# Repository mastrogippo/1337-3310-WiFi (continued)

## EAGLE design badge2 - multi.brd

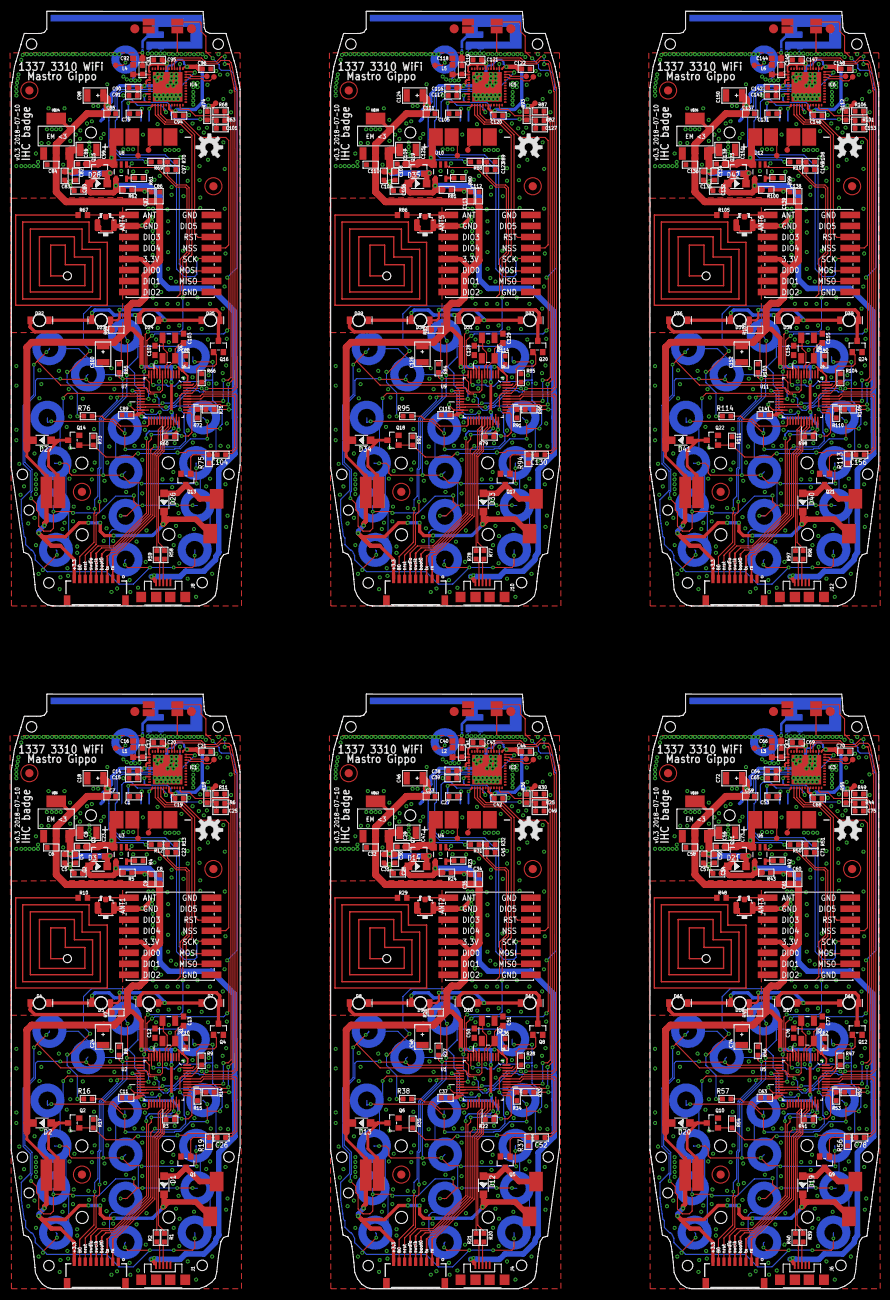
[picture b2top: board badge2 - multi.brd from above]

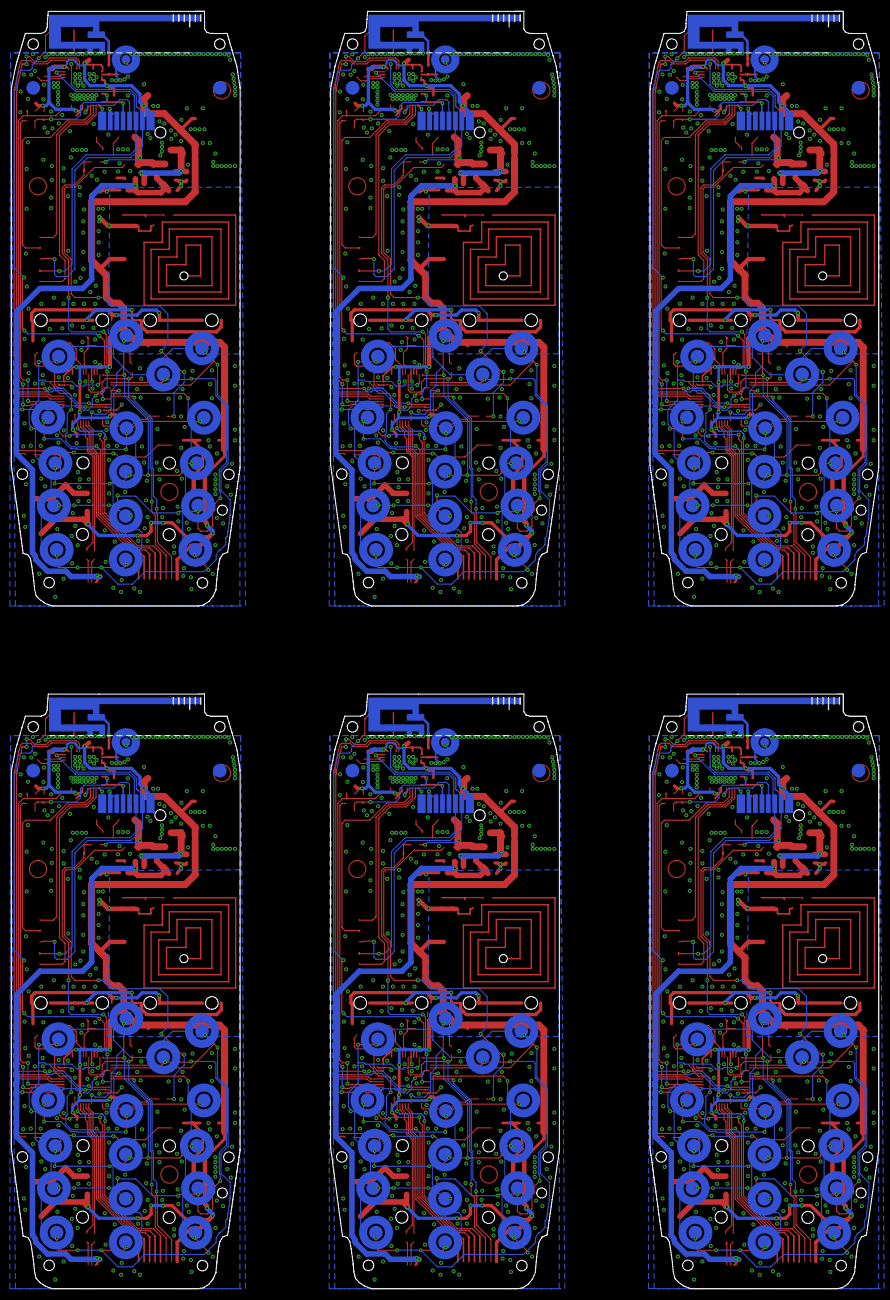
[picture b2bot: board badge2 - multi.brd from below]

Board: 2 copper layers, 157.6 x 232.0 mm, 474 parts (12 on the bottom side), 378 nets.

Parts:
ANT1, ANT2, ANT3, ANT4, ANT5, ANT6: U-FL; U-FL3P-SMD-2.6X2.6X1.0MM
C1, C2, C3, C4, C6, C7, C8, C21, C26, C27, C28, C29, C30, C32, C33, C34, C44, C52, C53, C54, C55, C56, C58, C59, C60, C70, C78, C79, C80, C81, C82, C84, C85, C86, C96, C104, C105, C106, C107, C108, C110, C111, C112, C122, C130, C131, C132, C133, C134, C136, C137, C138, C148, C156: 4.7uf; C0603
C5, C9, C10, C11, C15, C19, C20, C22, C25, C31, C35, C36, C37, C39, C42, C43, C45, C49, C57, C61, C62, C63, C65, C68, C69, C71, C75, C83, C87, C88, C89, C91, C94, C95, C97, C101, C109, C113, C114, C115, C117, C120, C121, C123, C127, C135, C139, C140, C141, C143, C146, C147, C149, C153: 100nf; C0603
C12, C13, C50, C51, C76, C77, C102, C103, C128, C129, C154, C155: 18pF; 0603
C14, C38, C64, C90, C116, C142: 10uf; C0603
C16, C40, C66, C92, C118, C144: 2.7p; C0603
C17, C41, C67, C93, C119, C145: 4.7PF; C0603
C18, C23, C24, C46, C47, C48, C72, C73, C74, C98, C99, C100, C124, C125, C126, C150, C151, C152: 22uf; AVX-B
D1, D2, D3, D12, D13, D14, D19, D20, D21, D26, D27, D28, D33, D34, D35, D40, D41, D42: NRVTS245ESFT3G; SOD-123
D4, D5, D6, D7, D8, D9, D10, D11, D15, D16, D17, D18, D22, D23, D24, D25, D29, D30, D31, D32, D36, D37, D38, D39: LED-BOTTOM-1206; LED-1206
FID1, FID2, FID3, FID4, FID5, FID6, FID7, FID8, FID9, FID10, FID11, FID12, FID13, FID14, FID15, FID16, FID17, FID18: FIDUCIAL1.5X3; FIDUCIAL-1.5X3
IC1, IC2, IC3, IC4, IC5, IC6: ESP32-PICO-D4; ESP32-PICO-D4_1
J1, J4, J6, J8, J10, J12: USB-MICROB
J2, J3, J5, J7, J9, J11: 1X01_POGOPIN_HOLE_0.58_DIA
L1, L2, L3, L4, L5, L6: 1.6nH; C0603K
Q1, Q2, Q4, Q5, Q6, Q8, Q9, Q10, Q12, Q13, Q14, Q16, Q17, Q18, Q20, Q21, Q22, Q24: CJ2302; SOT-23
Q3, Q7, Q11, Q15, Q19, Q23: FDN340P; SOT-23
R1, R2, R6, R7, R20, R21, R25, R26, R39, R40, R44, R45, R58, R59, R63, R64, R77, R78, R82, R83, R96, R97, R101, R102: 22R; R0603
R3, R22, R41, R60, R79, R98: 1.5K; R0603
R4, R23, R42, R61, R80, R99: 2K; R0603
R5, R9, R11, R16, R18, R19, R24, R28, R30, R36, R37, R38, R43, R47, R49, R55, R56, R57, R62, R66, R68, R74, R75, R76, R81, R85, R87, R93, R94, R95, R100, R104, R106, R112, R113, R114: 10K; R0603
R8, R27, R46, R65, R84, R103: 10K 1/10W; R0603
R10, R29, R48, R67, R86, R105: 0; R0603
R12, R13, R14, R15, R17, R31, R32, R33, R34, R35, R50, R51, R52, R53, R54, R69, R70, R71, R72, R73, R88, R89, R90, R91, R92, R107, R108, R109, R110, R111: 100K 1/10W; R0603
TP1, TP2, TP3, TP4, TP5, TP6, TP7, TP8, TP9, TP10, TP11, TP12, TP13, TP14, TP15, TP16, TP17, TP18, TP19, TP20, TP21, TP22, TP23, TP24, TP25, TP26, TP27, TP28, TP29, TP30, TP31, TP32, TP33, TP34, TP35, TP36: TEST-POINT3X4; PAD.03X.04
U1, U2, U5, U7, U9, U11: STM32F103CBT6; QFP50P900X900X160-48N
U3, U4, U6, U8, U10, U12: MCP73831; SOT23-5
U$1, U$7, U$13, U$19, U$25, U$31: 3310PANEL; 3310LCD
U$2, U$8, U$14, U$20, U$26, U$32: WIRELESS-LORA-RFM95W#SMD
U$3, U$9, U$15, U$21, U$27, U$33: INVERTED_F_ANTENNA+2; DN007+2
U$4, U$10, U$16, U$22, U$28, U$34: JST-09-PIN-HORIZONTAL; JST-09-SMD-HORI-1.0MM
U$5, U$11, U$17, U$23, U$29, U$35: OSHW-LOGO-M
U$6, U$12, U$18, U$24, U$30, U$36: CJT1117-3.3-SOT223; SOT-223
Y1, Y2, Y3, Y4, Y5, Y6: 8MHz; CRYSTAL-SMD-5X3.2-4PAD

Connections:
+3V1: C32.1, C33.1, C34.1, C35.1, C36.1, C37.1, C38.1, C39.1, C42.1, C43.1, C44.1, C46.+, C48.+, D12.-, D13.-, IC2.1, IC2.3, IC2.4, IC2.19, IC2.37, IC2.43, IC2.46, R22.2, R26.2, R27.2, R30.1, R36.2, TP9.P$1, U1.1, U1.9, U1.24, U1.36, U1.48, U$7.BUZ2, U$7.MOT2, U$7.P$8, U$8.B4, U$10.9, U$12.2, U$12.TER
+3V2: C58.1, C59.1, C60.1, C61.1, C62.1, C63.1, C64.1, C65.1, C68.1, C69.1, C70.1, C72.+, C74.+, D19.-, D20.-, IC3.1, IC3.3, IC3.4, IC3.19, IC3.37, IC3.43, IC3.46, R41.2, R45.2, R46.2, R49.1, R55.2, TP15.P$1, U5.1, U5.9, U5.24, U5.36, U5.48, U$13.BUZ2, U$13.MOT2, U$13.P$8, U$14.B4, U$16.9, U$18.2, U$18.TER
+3V3: C6.1, C7.1, C8.1, C9.1, C10.1, C11.1, C14.1, C15.1, C18.+, C19.1, C20.1, C21.1, C24.+, D1.-, D2.-, IC1.1, IC1.3, IC1.4, IC1.19, IC1.37, IC1.43, IC1.46, R3.2, R7.2, R8.2, R11.1, R18.2, TP3.P$1, U2.1, U2.9, U2.24, U2.36, U2.48, U$1.BUZ2, U$1.MOT2, U$1.P$8, U$2.B4, U$4.9, U$6.2, U$6.TER
+3V4: C84.1, C85.1, C86.1, C87.1, C88.1, C89.1, C90.1, C91.1, C94.1, C95.1, C96.1, C98.+, C100.+, D26.-, D27.-, IC4.1, IC4.3, IC4.4, IC4.19, IC4.37, IC4.43, IC4.46, R60.2, R64.2, R65.2, R68.1, R74.2, TP21.P$1, U7.1, U7.9, U7.24, U7.36, U7.48, U$19.BUZ2, U$19.MOT2, U$19.P$8, U$20.B4, U$22.9, U$24.2, U$24.TER
+3V5: C110.1, C111.1, C112.1, C113.1, C114.1, C115.1, C116.1, C117.1, C120.1, C121.1, C122.1, C124.+, C126.+, D33.-, D34.-, IC5.1, IC5.3, IC5.4, IC5.19, IC5.37, IC5.43, IC5.46, R79.2, R83.2, R84.2, R87.1, R93.2, TP27.P$1, U9.1, U9.9, U9.24, U9.36, U9.48, U$25.BUZ2, U$25.MOT2, U$25.P$8, U$26.B4, U$28.9, U$30.2, U$30.TER
+3V6: C136.1, C137.1, C138.1, C139.1, C140.1, C141.1, C142.1, C143.1, C146.1, C147.1, C148.1, C150.+, C152.+, D40.-, D41.-, IC6.1, IC6.3, IC6.4, IC6.19, IC6.37, IC6.43, IC6.46, R98.2, R102.2, R103.2, R106.1, R112.2, TP33.P$1, U11.1, U11.9, U11.24, U11.36, U11.48, U$31.BUZ2, U$31.MOT2, U$31.P$8, U$32.B4, U$34.9, U$36.2, U$36.TER
+5V: C2.1, D3.+, J1.VBUS, Q3.1, R5.2, R14.2, U3.4
+5V1: C28.1, D14.+, J4.VBUS, Q7.1, R24.2, R33.2, U4.4
+5V2: C54.1, D21.+, J6.VBUS, Q11.1, R43.2, R52.2, U6.4
+5V3: C80.1, D28.+, J8.VBUS, Q15.1, R62.2, R71.2, U8.4
+5V4: C106.1, D35.+, J10.VBUS, Q19.1, R81.2, R90.2, U10.4
+5V5: C132.1, D42.+, J12.VBUS, Q23.1, R100.2, R109.2, U12.4
ANT: J3.1, R10.1
ANT1: J2.1, R29.1
ANT2: J5.1, R48.1
ANT3: J7.1, R67.1
ANT4: J9.1, R86.1
ANT5: J11.1, R105.1
BOOT0: R9.2, U2.44, U$4.4
BOOT3: R28.2, U1.44, U$10.4
BOOT5: R47.2, U5.44, U$16.4
BOOT7: R66.2, U7.44, U$22.4
BOOT9: R85.2, U9.44, U$28.4
BOOT11: R104.2, U11.44, U$34.4
BUZ: C26.1, U2.43
BUZ1: C52.1, U1.43
BUZ2: C78.1, U5.43
BUZ3: C104.1, U7.43
BUZ4: C130.1, U9.43
BUZ5: C156.1, U11.43
CS_LCD: IC1.12, U$1.P$4
CS_LCD1: IC2.12, U$7.P$4
CS_LCD2: IC3.12, U$13.P$4
CS_LCD3: IC4.12, U$19.P$4
CS_LCD4: IC5.12, U$25.P$4
CS_LCD5: IC6.12, U$31.P$4
CS_LORA: IC1.16, U$2.A5
CS_LORA1: IC2.16, U$8.A5
CS_LORA2: IC3.16, U$14.A5
CS_LORA3: IC4.16, U$20.A5
CS_LORA4: IC5.16, U$26.A5
CS_LORA5: IC6.16, U$32.A5
C_STAT: R16.1, U2.25
C_STAT1: R38.1, U1.25
C_STAT2: R57.1, U5.25
C_STAT3: R76.1, U7.25
C_STAT4: R95.1, U9.25
C_STAT5: R114.1, U11.25
D+: R1.2, R3.1, U2.33
D+1: R20.2, R22.1, U1.33
D+2: R39.2, R41.1, U5.33
D+3: R58.2, R60.1, U7.33
D+4: R77.2, R79.1, U9.33
D+5: R96.2, R98.1, U11.33
D-: R2.2, U2.32
D-1: R21.2, U1.32
D-2: R40.2, U5.32
D-3: R59.2, U7.32
D-4: R78.2, U9.32
D-5: R97.2, U11.32
D_E_LCD: IC1.17, U$1.P$5
D_E_LCD1: IC2.17, U$7.P$5
D_E_LCD2: IC3.17, U$13.P$5
D_E_LCD3: IC4.17, U$19.P$5
D_E_LCD4: IC5.17, U$25.P$5
D_E_LCD5: IC6.17, U$31.P$5
ESP_B0: IC1.23, R11.2, U2.40
ESP_B1: IC2.23, R30.2, U1.40
ESP_B2: IC3.23, R49.2, U5.40
ESP_B3: IC4.23, R68.2, U7.40
ESP_B4: IC5.23, R87.2, U9.40
ESP_B5: IC6.23, R106.2, U11.40
ESP_RST: C25.1, IC1.9, R6.1, R18.1
ESP_RST1: C49.1, IC2.9, R25.1, R36.1
ESP_RST2: C75.1, IC3.9, R44.1, R55.1
ESP_RST3: C101.1, IC4.9, R63.1, R74.1
ESP_RST4: C127.1, IC5.9, R82.1, R93.1
ESP_RST5: C153.1, IC6.9, R101.1, R112.1
ESP_RX: IC1.40, U2.21
ESP_RX1: IC2.40, U1.21
ESP_RX2: IC3.40, U5.21
ESP_RX3: IC4.40, U7.21
ESP_RX4: IC5.40, U9.21
ESP_RX5: IC6.40, U11.21
ESP_TX: IC1.41, U2.22
ESP_TX1: IC2.41, U1.22
ESP_TX2: IC3.41, U5.22
ESP_TX3: IC4.41, U7.22
ESP_TX4: IC5.41, U9.22
ESP_TX5: IC6.41, U11.22
GND: ANT1.GND1, ANT1.GND2, C1.1, C2.2, C3.2, C4.2, C5.2, C6.2, C7.2, C8.2, C9.2, C10.2, C11.2, C12.1, C13.1, C14.2, C15.2, C16.2, C18.-, C19.2, C20.2, C21.2, C22.2, C23.-, C24.-, C25.2, IC1.49, J1.GND, J1.MT1, J1.MT2, J1.P$1, J1.P$2, L1.2, Q1.2, Q2.2, Q4.2, R4.1, R5.1, R9.1, R13.1, R15.1, R17.1, R19.2, U2.8, U2.23, U2.35, U2.47, U3.2, U$1.BATT-, U$1.G1, U$1.G2, U$1.P$3, U$1.PW2A, U$1.PW2B, U$1.SPK2, U$2.A1, U$2.A8, U$2.B7, U$3.GND, U$3.GND@1, U$4.1, U$4.M1, U$4.M2, U$6.1
GND1: ANT2.GND1, ANT2.GND2, C27.1, C28.2, C29.2, C30.2, C31.2, C32.2, C33.2, C34.2, C35.2, C36.2, C37.2, C38.2, C39.2, C40.2, C42.2, C43.2, C44.2, C45.2, C46.-, C47.-, C48.-, C49.2, C50.1, C51.1, IC2.49, J4.GND, J4.MT1, J4.MT2, J4.P$1, J4.P$2, L2.2, Q5.2, Q6.2, Q8.2, R23.1, R24.1, R28.1, R32.1, R34.1, R35.1, R37.2, U1.8, U1.23, U1.35, U1.47, U4.2, U$7.BATT-, U$7.G1, U$7.G2, U$7.P$3, U$7.PW2A, U$7.PW2B, U$7.SPK2, U$8.A1, U$8.A8, U$8.B7, U$9.GND, U$9.GND@1, U$10.1, U$10.M1, U$10.M2, U$12.1
GND2: ANT3.GND1, ANT3.GND2, C53.1, C54.2, C55.2, C56.2, C57.2, C58.2, C59.2, C60.2, C61.2, C62.2, C63.2, C64.2, C65.2, C66.2, C68.2, C69.2, C70.2, C71.2, C72.-, C73.-, C74.-, C75.2, C76.1, C77.1, IC3.49, J6.GND, J6.MT1, J6.MT2, J6.P$1, J6.P$2, L3.2, Q9.2, Q10.2, Q12.2, R42.1, R43.1, R47.1, R51.1, R53.1, R54.1, R56.2, U5.8, U5.23, U5.35, U5.47, U6.2, U$13.BATT-, U$13.G1, U$13.G2, U$13.P$3, U$13.PW2A, U$13.PW2B, U$13.SPK2, U$14.A1, U$14.A8, U$14.B7, U$15.GND, U$15.GND@1, U$16.1, U$16.M1, U$16.M2, U$18.1
GND3: ANT4.GND1, ANT4.GND2, C79.1, C80.2, C81.2, C82.2, C83.2, C84.2, C85.2, C86.2, C87.2, C88.2, C89.2, C90.2, C91.2, C92.2, C94.2, C95.2, C96.2, C97.2, C98.-, C99.-, C100.-, C101.2, C102.1, C103.1, IC4.49, J8.GND, J8.MT1, J8.MT2, J8.P$1, J8.P$2, L4.2, Q13.2, Q14.2, Q16.2, R61.1, R62.1, R66.1, R70.1, R72.1, R73.1, R75.2, U7.8, U7.23, U7.35, U7.47, U8.2, U$19.BATT-, U$19.G1, U$19.G2, U$19.P$3, U$19.PW2A, U$19.PW2B, U$19.SPK2, U$20.A1, U$20.A8, U$20.B7, U$21.GND, U$21.GND@1, U$22.1, U$22.M1, U$22.M2, U$24.1
GND4: ANT5.GND1, ANT5.GND2, C105.1, C106.2, C107.2, C108.2, C109.2, C110.2, C111.2, C112.2, C113.2, C114.2, C115.2, C116.2, C117.2, C118.2, C120.2, C121.2, C122.2, C123.2, C124.-, C125.-, C126.-, C127.2, C128.1, C129.1, IC5.49, J10.GND, J10.MT1, J10.MT2, J10.P$1, J10.P$2, L5.2, Q17.2, Q18.2, Q20.2, R80.1, R81.1, R85.1, R89.1, R91.1, R92.1, R94.2, U9.8, U9.23, U9.35, U9.47, U10.2, U$25.BATT-, U$25.G1, U$25.G2, U$25.P$3, U$25.PW2A, U$25.PW2B, U$25.SPK2, U$26.A1, U$26.A8, U$26.B7, U$27.GND, U$27.GND@1, U$28.1, U$28.M1, U$28.M2, U$30.1
GND5: ANT6.GND1, ANT6.GND2, C131.1, C132.2, C133.2, C134.2, C135.2, C136.2, C137.2, C138.2, C139.2, C140.2, C141.2, C142.2, C143.2, C144.2, C146.2, C147.2, C148.2, C149.2, C150.-, C151.-, C152.-, C153.2, C154.1, C155.1, IC6.49, J12.GND, J12.MT1, J12.MT2, J12.P$1, J12.P$2, L6.2, Q21.2, Q22.2, Q24.2, R99.1, R100.1, R104.1, R108.1, R110.1, R111.1, R113.2, U11.8, U11.23, U11.35, U11.47, U12.2, U$31.BATT-, U$31.G1, U$31.G2, U$31.P$3, U$31.PW2A, U$31.PW2B, U$31.SPK2, U$32.A1, U$32.A8, U$32.B7, U$33.GND, U$33.GND@1, U$34.1, U$34.M1, U$34.M2, U$36.1
IO5: IC1.34, TP1.P$1
IO7: IC2.34, TP7.P$1
IO8: IC2.35, TP8.P$1
IO14: IC3.34, TP13.P$1
IO15: IC3.35, TP14.P$1
IO18: IC1.35, TP2.P$1
IO22: IC4.34, TP19.P$1
IO23: IC4.35, TP20.P$1
IO29: IC5.34, TP25.P$1
IO30: IC5.35, TP26.P$1
IO41: IC6.34, TP31.P$1
IO42: IC6.35, TP32.P$1
KP: U2.10, U$1.PW1A, U$1.PW1B
KP1: U1.10, U$7.PW1A, U$7.PW1B
KP2: U5.10, U$13.PW1A, U$13.PW1B
KP3: U7.10, U$19.PW1A, U$19.PW1B
KP4: U9.10, U$25.PW1A, U$25.PW1B
KP5: U11.10, U$31.PW1A, U$31.PW1B
KX1: U2.11, U$1.B1I, U$1.B2I, U$1.B3I, U$1.BCI
KX2: U2.12, U$1.B4I, U$1.B5I, U$1.B6I, U$1.BMI
KX3: U2.13, U$1.B7I, U$1.B8I, U$1.B9I, U$1.BDI
KX4: U2.14, U$1.B0I, U$1.BAI, U$1.BSI, U$1.BUI
KX5: U1.11, U$7.B1I, U$7.B2I, U$7.B3I, U$7.BCI
KX6: U1.12, U$7.B4I, U$7.B5I, U$7.B6I, U$7.BMI
KX7: U1.13, U$7.B7I, U$7.B8I, U$7.B9I, U$7.BDI
KX8: U1.14, U$7.B0I, U$7.BAI, U$7.BSI, U$7.BUI
KX9: U5.11, U$13.B1I, U$13.B2I, U$13.B3I, U$13.BCI
KX10: U5.12, U$13.B4I, U$13.B5I, U$13.B6I, U$13.BMI
KX11: U5.13, U$13.B7I, U$13.B8I, U$13.B9I, U$13.BDI
KX12: U5.14, U$13.B0I, U$13.BAI, U$13.BSI, U$13.BUI
KX13: U7.11, U$19.B1I, U$19.B2I, U$19.B3I, U$19.BCI
KX14: U7.12, U$19.B4I, U$19.B5I, U$19.B6I, U$19.BMI
KX15: U7.13, U$19.B7I, U$19.B8I, U$19.B9I, U$19.BDI
KX16: U7.14, U$19.B0I, U$19.BAI, U$19.BSI, U$19.BUI
KX17: U9.11, U$25.B1I, U$25.B2I, U$25.B3I, U$25.BCI
KX18: U9.12, U$25.B4I, U$25.B5I, U$25.B6I, U$25.BMI
KX19: U9.13, U$25.B7I, U$25.B8I, U$25.B9I, U$25.BDI
KX20: U9.14, U$25.B0I, U$25.BAI, U$25.BSI, U$25.BUI
KX21: U11.11, U$31.B1I, U$31.B2I, U$31.B3I, U$31.BCI
KX22: U11.12, U$31.B4I, U$31.B5I, U$31.B6I, U$31.BMI
KX23: U11.13, U$31.B7I, U$31.B8I, U$31.B9I, U$31.BDI
KX24: U11.14, U$31.B0I, U$31.BAI, U$31.BSI, U$31.BUI
KY1: U2.15, U$1.B1O, U$1.B4O, U$1.B7O, U$1.BAO
KY2: U2.16, U$1.B0O, U$1.B2O, U$1.B5O, U$1.B8O
KY3: U2.17, U$1.B3O, U$1.B6O, U$1.B9O, U$1.BSO
KY4: U2.29, U$1.BCO, U$1.BDO, U$1.BMO, U$1.BUO
KY5: U1.15, U$7.B1O, U$7.B4O, U$7.B7O, U$7.BAO
KY6: U1.16, U$7.B0O, U$7.B2O, U$7.B5O, U$7.B8O
KY7: U1.17, U$7.B3O, U$7.B6O, U$7.B9O, U$7.BSO
KY8: U1.29, U$7.BCO, U$7.BDO, U$7.BMO, U$7.BUO
KY9: U5.15, U$13.B1O, U$13.B4O, U$13.B7O, U$13.BAO
KY10: U5.16, U$13.B0O, U$13.B2O, U$13.B5O, U$13.B8O
KY11: U5.17, U$13.B3O, U$13.B6O, U$13.B9O, U$13.BSO
KY12: U5.29, U$13.BCO, U$13.BDO, U$13.BMO, U$13.BUO
KY13: U7.15, U$19.B1O, U$19.B4O, U$19.B7O, U$19.BAO
KY14: U7.16, U$19.B0O, U$19.B2O, U$19.B5O, U$19.B8O
KY15: U7.17, U$19.B3O, U$19.B6O, U$19.B9O, U$19.BSO
KY16: U7.29, U$19.BCO, U$19.BDO, U$19.BMO, U$19.BUO
KY17: U9.15, U$25.B1O, U$25.B4O, U$25.B7O, U$25.BAO
KY18: U9.16, U$25.B0O, U$25.B2O, U$25.B5O, U$25.B8O
KY19: U9.17, U$25.B3O, U$25.B6O, U$25.B9O, U$25.BSO
KY20: U9.29, U$25.BCO, U$25.BDO, U$25.BMO, U$25.BUO
KY21: U11.15, U$31.B1O, U$31.B4O, U$31.B7O, U$31.BAO
KY22: U11.16, U$31.B0O, U$31.B2O, U$31.B5O, U$31.B8O
KY23: U11.17, U$31.B3O, U$31.B6O, U$31.B9O, U$31.BSO
KY24: U11.29, U$31.BCO, U$31.BDO, U$31.BMO, U$31.BUO
LED: Q4.1, U2.46
LED1: Q8.1, U1.46
LED2: Q12.1, U5.46
LED3: Q16.1, U7.46
LED4: Q20.1, U9.46
LED5: Q24.1, U11.46
MISO: IC1.14, U$2.A2
MISO1: IC2.14, U$8.A2
MISO2: IC3.14, U$14.A2
MISO3: IC4.14, U$20.A2
MISO4: IC5.14, U$26.A2
MISO5: IC6.14, U$32.A2
MOSI: IC1.36, U$1.P$6, U$2.A3
MOSI1: IC2.36, U$7.P$6, U$8.A3
MOSI2: IC3.36, U$13.P$6, U$14.A3
MOSI3: IC4.36, U$19.P$6, U$20.A3
MOSI4: IC5.36, U$25.P$6, U$26.A3
MOSI5: IC6.36, U$31.P$6, U$32.A3
MOT: Q2.1, R17.2, U2.42
MOT1: Q6.1, R35.2, U1.42
MOT2: Q10.1, R54.2, U5.42
MOT3: Q14.1, R73.2, U7.42
MOT4: Q18.1, R92.2, U9.42
MOT5: Q22.1, R111.2, U11.42
unnamed: C1.2, U$1.P$2
unnamed: C16.1, C17.1, U$3.FEED
unnamed: C17.2, IC1.2, L1.1
unnamed: ANT1.D, R10.2, U$2.B8
unnamed: J1.D+, R1.1
unnamed: J1.D-, R2.1
unnamed: R16.2, U3.1
unnamed: C26.2, Q1.1, R19.1
unnamed: D1.+, Q1.3, U$1.BUZ1
unnamed: C13.2, U2.5, Y1.3
unnamed: TP4.P$1, U$1.BTEMP
unnamed: D2.+, Q2.3, U$1.MOT1
unnamed: R4.2, U3.5
unnamed: C4.1, C5.1, C23.+, D3.-, Q3.2, U$6.3
unnamed: C12.2, U2.6, Y1.1
unnamed: U2.18, U$4.8
unnamed: TP6.P$1, U$1.SPK1
unnamed: C27.2, U$7.P$2
unnamed: R6.2, U2.41
unnamed: TP5.P$1, U$1.B_SI
unnamed: D4.C, D5.C, D6.C, D7.C, Q4.3
unnamed: D4.A, D5.A, D6.A, D7.A, R7.1
unnamed: C22.1, R12.1, R13.2, U2.19
unnamed: J4.D+, R20.1
unnamed: J4.D-, R21.1
unnamed: D12.+, Q5.3, U$7.BUZ1
unnamed: D13.+, Q6.3, U$7.MOT1
unnamed: R23.2, U4.5
unnamed: C30.1, C31.1, C47.+, D14.-, Q7.2, U$12.3
unnamed: C40.1, C41.1, U$9.FEED
unnamed: C41.2, IC2.2, L2.1
unnamed: R25.2, U1.41
unnamed: D8.C, D9.C, D10.C, D11.C, Q8.3
unnamed: D8.A, D9.A, D10.A, D11.A, R26.1
unnamed: ANT2.D, R29.2, U$8.B8
unnamed: U1.18, U$10.8
unnamed: C45.1, R31.1, R32.2, U1.19
unnamed: TP10.P$1, U$7.BTEMP
unnamed: TP11.P$1, U$7.B_SI
unnamed: TP12.P$1, U$7.SPK1
unnamed: C51.2, U1.5, Y2.3
unnamed: C50.2, U1.6, Y2.1
unnamed: C52.2, Q5.1, R37.1
unnamed: R38.2, U4.1
unnamed: C53.2, U$13.P$2
unnamed: J6.D+, R39.1
unnamed: J6.D-, R40.1
unnamed: D19.+, Q9.3, U$13.BUZ1
unnamed: D20.+, Q10.3, U$13.MOT1
unnamed: R42.2, U6.5
unnamed: C56.1, C57.1, C73.+, D21.-, Q11.2, U$18.3
unnamed: C66.1, C67.1, U$15.FEED
unnamed: C67.2, IC3.2, L3.1
unnamed: R44.2, U5.41
unnamed: D15.C, D16.C, D17.C, D18.C, Q12.3
unnamed: D15.A, D16.A, D17.A, D18.A, R45.1
unnamed: ANT3.D, R48.2, U$14.B8
unnamed: U5.18, U$16.8
unnamed: C71.1, R50.1, R51.2, U5.19
unnamed: TP16.P$1, U$13.BTEMP
unnamed: TP17.P$1, U$13.B_SI
unnamed: TP18.P$1, U$13.SPK1
unnamed: C77.2, U5.5, Y3.3
unnamed: C76.2, U5.6, Y3.1
unnamed: C78.2, Q9.1, R56.1
unnamed: R57.2, U6.1
unnamed: C79.2, U$19.P$2
unnamed: J8.D+, R58.1
unnamed: J8.D-, R59.1
unnamed: D26.+, Q13.3, U$19.BUZ1
unnamed: D27.+, Q14.3, U$19.MOT1
unnamed: R61.2, U8.5
unnamed: C82.1, C83.1, C99.+, D28.-, Q15.2, U$24.3
unnamed: C92.1, C93.1, U$21.FEED
unnamed: C93.2, IC4.2, L4.1
unnamed: R63.2, U7.41
unnamed: D22.C, D23.C, D24.C, D25.C, Q16.3
unnamed: D22.A, D23.A, D24.A, D25.A, R64.1
unnamed: ANT4.D, R67.2, U$20.B8
unnamed: U7.18, U$22.8
unnamed: C97.1, R69.1, R70.2, U7.19
unnamed: TP22.P$1, U$19.BTEMP
unnamed: TP23.P$1, U$19.B_SI
unnamed: TP24.P$1, U$19.SPK1
unnamed: C103.2, U7.5, Y4.3
unnamed: C102.2, U7.6, Y4.1
unnamed: C104.2, Q13.1, R75.1
unnamed: R76.2, U8.1
unnamed: C105.2, U$25.P$2
unnamed: J10.D+, R77.1
unnamed: J10.D-, R78.1
unnamed: D33.+, Q17.3, U$25.BUZ1
unnamed: D34.+, Q18.3, U$25.MOT1
unnamed: R80.2, U10.5
unnamed: C108.1, C109.1, C125.+, D35.-, Q19.2, U$30.3
unnamed: C118.1, C119.1, U$27.FEED
unnamed: C119.2, IC5.2, L5.1
unnamed: R82.2, U9.41
unnamed: D29.C, D30.C, D31.C, D32.C, Q20.3
unnamed: D29.A, D30.A, D31.A, D32.A, R83.1
unnamed: ANT5.D, R86.2, U$26.B8
unnamed: U9.18, U$28.8
unnamed: C123.1, R88.1, R89.2, U9.19
unnamed: TP28.P$1, U$25.BTEMP
unnamed: TP29.P$1, U$25.B_SI
unnamed: TP30.P$1, U$25.SPK1
unnamed: C129.2, U9.5, Y5.3
unnamed: C128.2, U9.6, Y5.1
unnamed: C130.2, Q17.1, R94.1
unnamed: R95.2, U10.1
unnamed: C131.2, U$31.P$2
unnamed: J12.D+, R96.1
unnamed: J12.D-, R97.1
unnamed: D40.+, Q21.3, U$31.BUZ1
unnamed: D41.+, Q22.3, U$31.MOT1
unnamed: R99.2, U12.5
unnamed: C134.1, C135.1, C151.+, D42.-, Q23.2, U$36.3
unnamed: C144.1, C145.1, U$33.FEED
unnamed: C145.2, IC6.2, L6.1
unnamed: R101.2, U11.41
unnamed: D36.C, D37.C, D38.C, D39.C, Q24.3
unnamed: D36.A, D37.A, D38.A, D39.A, R102.1
unnamed: ANT6.D, R105.2, U$32.B8
unnamed: U11.18, U$34.8
unnamed: C149.1, R107.1, R108.2, U11.19
unnamed: TP34.P$1, U$31.BTEMP
unnamed: TP35.P$1, U$31.B_SI
unnamed: TP36.P$1, U$31.SPK1
unnamed: C155.2, U11.5, Y6.3
unnamed: C154.2, U11.6, Y6.1
unnamed: C156.2, Q21.1, R113.1
unnamed: R114.2, U12.1
NRST: R8.1, U2.7, U$4.7
NRST1: R27.1, U1.7, U$10.7
NRST2: R46.1, U5.7, U$16.7
NRST3: R65.1, U7.7, U$22.7
NRST4: R84.1, U9.7, U$28.7
NRST5: R103.1, U11.7, U$34.7
RES_LCD: IC1.13, U$1.P$1
RES_LCD1: IC2.13, U$7.P$1
RES_LCD2: IC3.13, U$13.P$1
RES_LCD3: IC4.13, U$19.P$1
RES_LCD4: IC5.13, U$25.P$1
RES_LCD5: IC6.13, U$31.P$1
RST_LORA: IC1.15, U$2.A6
RST_LORA1: IC2.15, U$8.A6
RST_LORA2: IC3.15, U$14.A6
RST_LORA3: IC4.15, U$20.A6
RST_LORA4: IC5.15, U$26.A6
RST_LORA5: IC6.15, U$32.A6
SCLK: IC1.38, U$1.P$7, U$2.A4
SCLK1: IC2.38, U$7.P$7, U$8.A4
SCLK2: IC3.38, U$13.P$7, U$14.A4
SCLK3: IC4.38, U$19.P$7, U$20.A4
SCLK4: IC5.38, U$25.P$7, U$26.A4
SCLK5: IC6.38, U$31.P$7, U$32.A4
SWCLK: U2.37, U$4.5
SWCLK1: U1.37, U$10.5
SWCLK2: U5.37, U$16.5
SWCLK3: U7.37, U$22.5
SWCLK4: U9.37, U$28.5
SWCLK5: U11.37, U$34.5
SWDIO: U2.34, U$4.6
SWDIO1: U1.34, U$10.6
SWDIO2: U5.34, U$16.6
SWDIO3: U7.34, U$22.6
SWDIO4: U9.34, U$28.6
SWDIO5: U11.34, U$34.6
S_RX: U2.31, U$4.2
S_RX1: U1.31, U$10.2
S_RX2: U5.31, U$16.2
S_RX3: U7.31, U$22.2
S_RX4: U9.31, U$28.2
S_RX5: U11.31, U$34.2
S_TX: U2.30, U$4.3
S_TX1: U1.30, U$10.3
S_TX2: U5.30, U$16.3
S_TX3: U7.30, U$22.3
S_TX4: U9.30, U$28.3
S_TX5: U11.30, U$34.3
USB_PRES: R14.1, R15.2, U2.39
USB_PRES1: R33.1, R34.2, U1.39
USB_PRES2: R52.1, R53.2, U5.39
USB_PRES3: R71.1, R72.2, U7.39
USB_PRES4: R90.1, R91.2, U9.39
USB_PRES5: R109.1, R110.2, U11.39
VBAT: C3.1, Q3.3, R12.2, U3.3, U$1.BATT+
VBAT1: C29.1, Q7.3, R31.2, U4.3, U$7.BATT+
VBAT2: C55.1, Q11.3, R50.2, U6.3, U$13.BATT+
VBAT3: C81.1, Q15.3, R69.2, U8.3, U$19.BATT+
VBAT4: C107.1, Q19.3, R88.2, U10.3, U$25.BATT+
VBAT5: C133.1, Q23.3, R107.2, U12.3, U$31.BATT+

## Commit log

2018-07-19 First production version
2019-08-09 Added license
2022-01-11 Add link to STM32 firmware
